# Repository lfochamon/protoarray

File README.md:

# ProtoArray: A prototype microphone array for the BeagleBone Black

This repository contains a prototype ADS131E08 cape for the BBB to be used as a microphone array (or whatever).

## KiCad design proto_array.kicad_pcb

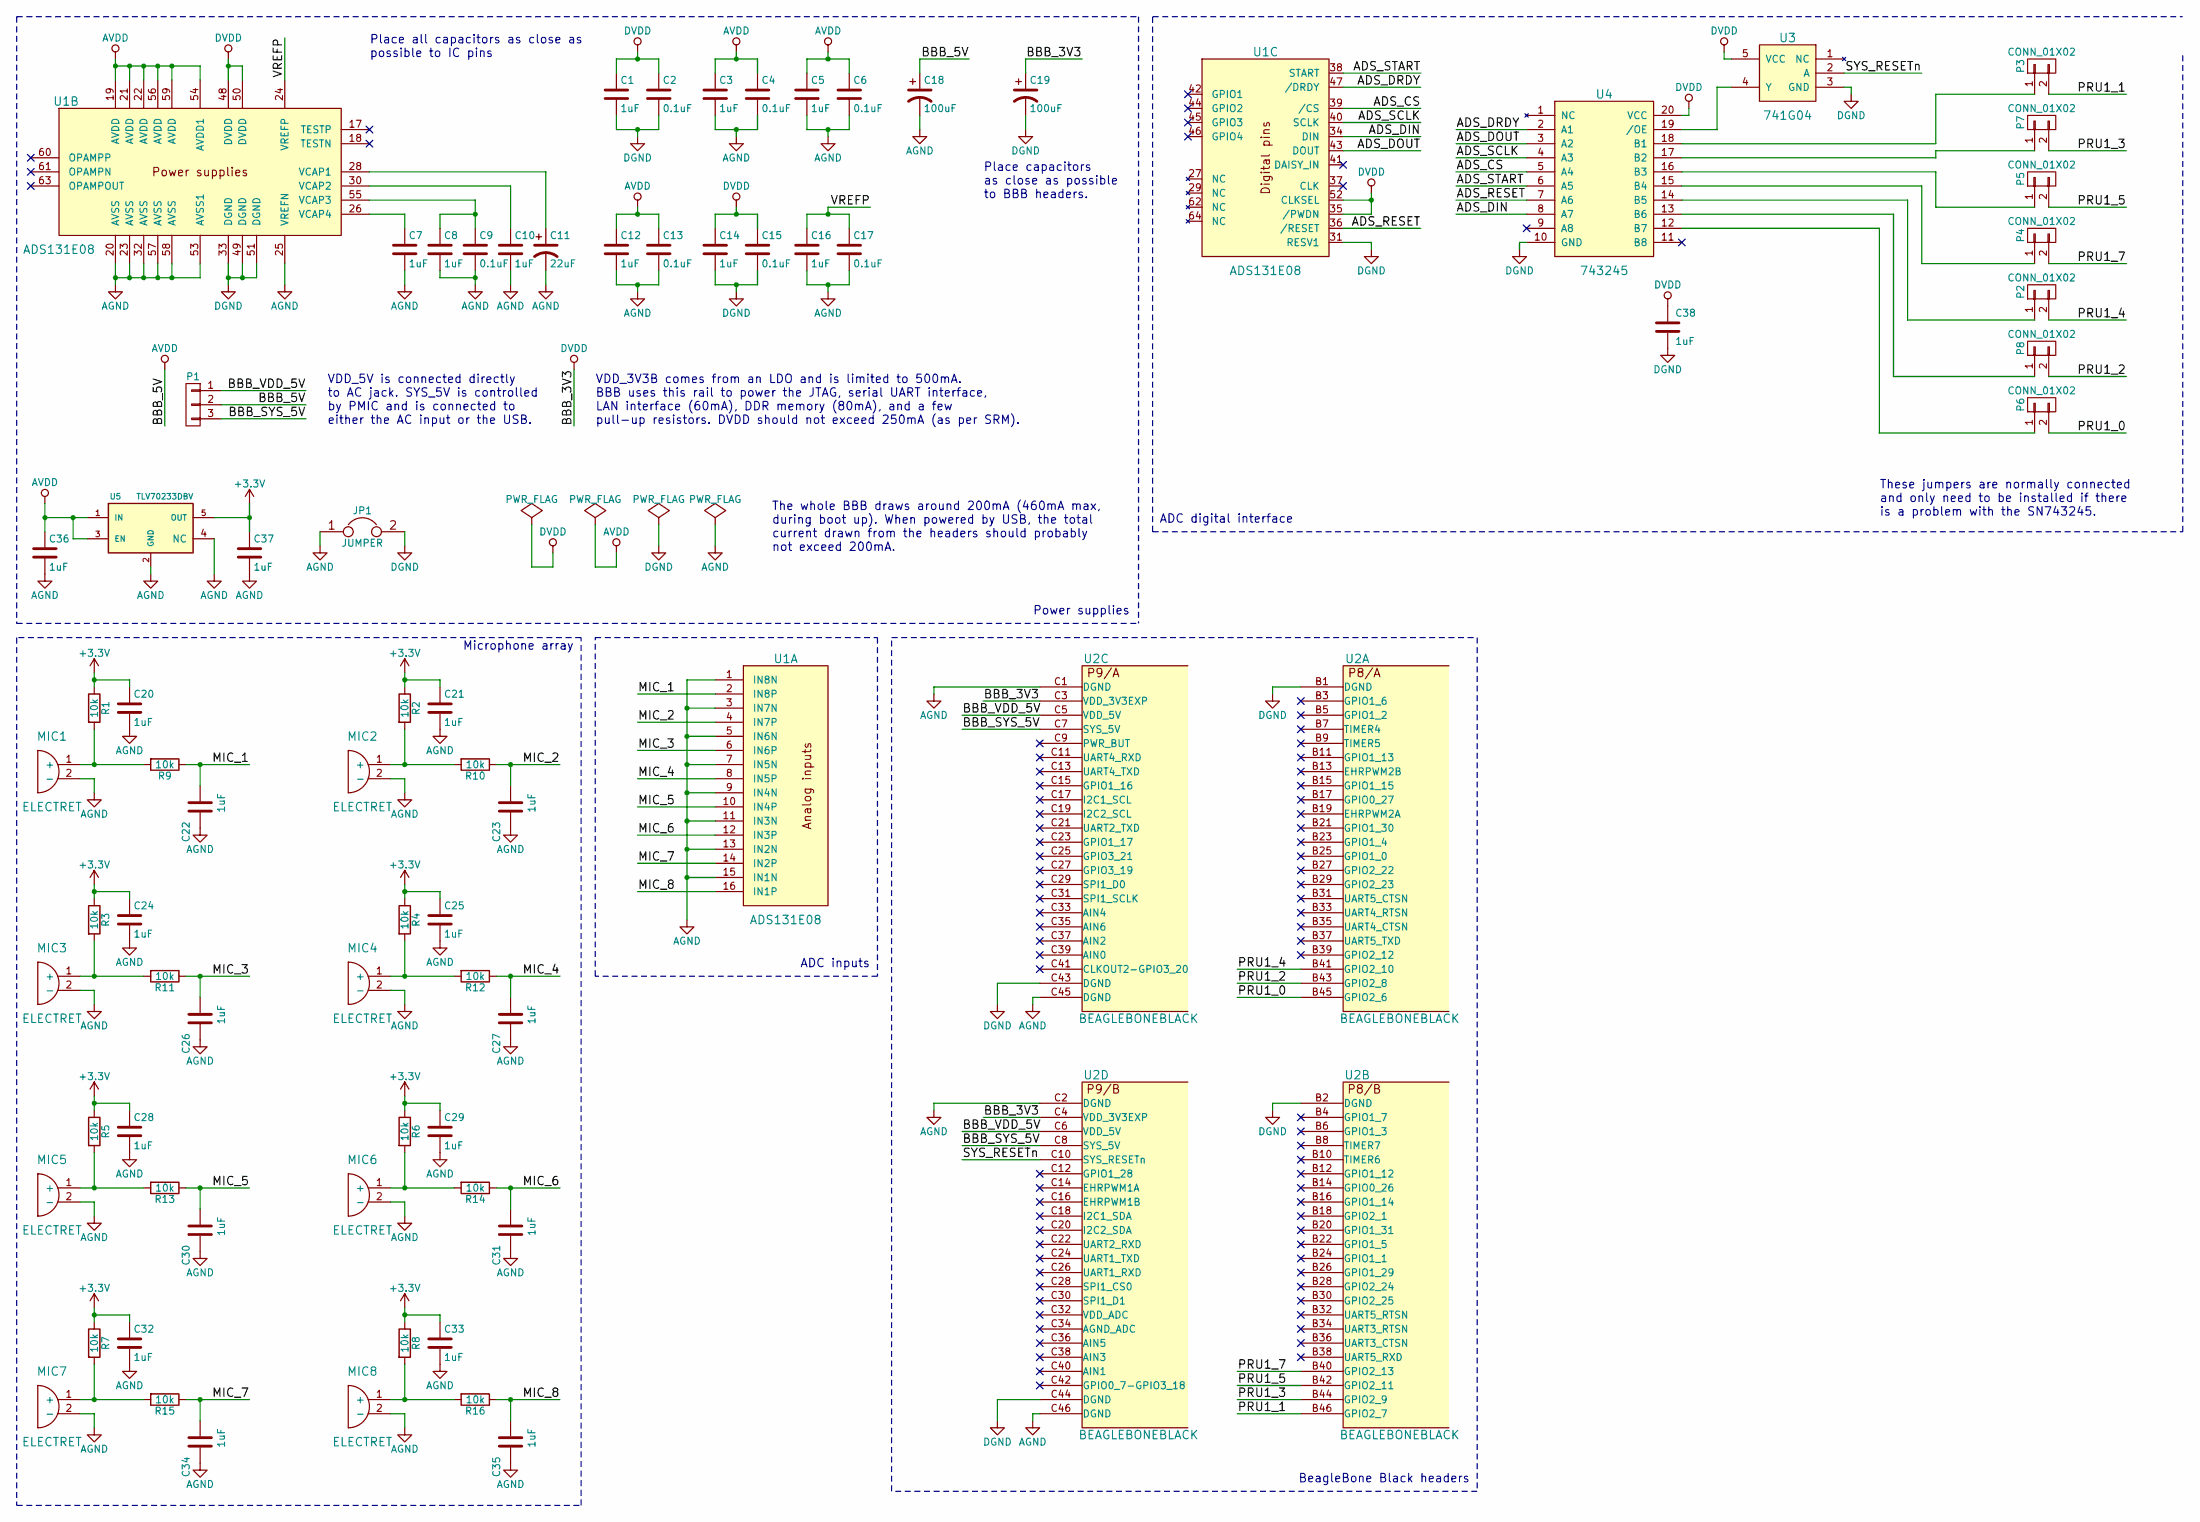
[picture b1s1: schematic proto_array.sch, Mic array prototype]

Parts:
C1, C3, C5, C7, C8, C10, C12, C14, C16, C20, C21, C22, C23, C24, C25, C26, C27, C28, C29, C30, C31, C32, C33, C34, C35, C36, C37, C38: 1uF; C_0805_HandSoldering
C2, C4, C6, C9, C13, C15, C17: 0.1uF; C_0805_HandSoldering
C11: 22uF; TantalC_SizeB_EIA-3528_HandSoldering
C18, C19: 100uF; Elko_vert_11.2x6.3mm_RM2.5_CopperClear
JP1: JUMPER; Jumper
MIC1, MIC2, MIC3, MIC4, MIC5, MIC6, MIC7, MIC8: ELECTRET; Electret_1mm
P1: CONN_01X03; Pin_Header_01x03
P2, P3, P4, P5, P6, P7, P8: CONN_01X02; Pin_Header_NC_01x02
R1, R2, R3, R4, R5, R6, R7, R8, R9, R10, R11, R12, R13, R14, R15, R16: 10k; R_0805_HandSoldering
U1: ADS131E08; LQFP-64_12x12_Pitch0.5mm_NoFid
U2: BEAGLEBONEBLACK; beagleboneblack_custom
U3: 741G04; SOTFL-5_160x50_Pitch0.5
U4: 743245; SOP-20_600x175_Pitch0.635
U5: TLV70233DBV; SOT-23-5

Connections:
+3V3: C20.1, C21.1, C24.1, C25.1, C28.1, C29.1, C32.1, C33.1, C37.1, R1.1, R2.1, R3.1, R4.1, R5.1, R6.1, R7.1, R8.1, U5.5 (OUT)
/ADS_CS: U1.39 (/CS), U4.5 (A4)
/ADS_DIN: U1.34 (DIN), U4.8 (A7)
/ADS_DOUT: U1.43 (DOUT), U4.3 (A2)
/ADS_DRDY: U1.47 (/DRDY), U4.2 (A1)
/ADS_RESET: U1.36 (/RESET), U4.7 (A6)
/ADS_SCLK: U1.40 (SCLK), U4.4 (A3)
/ADS_START: U1.38 (START), U4.6 (A5)
/BBB_SYS_5V: P1.3, U2.C7 (SYS_5V), U2.C8 (SYS_5V)
/BBB_VDD_5V: P1.1, U2.C5 (VDD_5V), U2.C6 (VDD_5V)
/MIC_1: C22.2, R9.1, U1.2 (IN8P)
/MIC_2: C23.2, R10.1, U1.4 (IN7P)
/MIC_3: C26.2, R11.1, U1.6 (IN6P)
/MIC_4: C27.2, R12.1, U1.8 (IN5P)
/MIC_5: C30.2, R13.1, U1.10 (IN4P)
/MIC_6: C31.2, R14.1, U1.12 (IN3P)
/MIC_7: C34.2, R15.1, U1.14 (IN2P)
/MIC_8: C35.2, R16.1, U1.16 (IN1P)
/PRU1_0: P6.2, U2.B45 (GPIO2_6)
/PRU1_1: P3.2, U2.B46 (GPIO2_7)
/PRU1_2: P8.2, U2.B43 (GPIO2_8)
/PRU1_3: P7.2, U2.B44 (GPIO2_9)
/PRU1_4: P2.2, U2.B41 (GPIO2_10)
/PRU1_5: P5.2, U2.B42 (GPIO2_11)
/PRU1_7: P4.2, U2.B40 (GPIO2_13)
/SYS_RESETn: U2.C10 (SYS_RESETn), U3.2 (A)
/VREFP: C16.1, C17.1, U1.24 (VREFP)
AGND: C3.2, C4.2, C5.2, C6.2, C7.2, C8.2, C9.2, C10.2, C11.2, C12.2, C13.2, C16.2, C17.2, C18.2, C20.2, C21.2, C22.1, C23.1, C24.2, C25.2, C26.1, C27.1, C28.2, C29.2, C30.1, C31.1, C32.2, C33.2, C34.1, C35.1, C36.2, C37.2, JP1.1, MIC1.2 (-), MIC2.2 (-), MIC3.2 (-), MIC4.2 (-), MIC5.2 (-), MIC6.2 (-), MIC7.2 (-), MIC8.2 (-), U1.1 (IN8N), U1.3 (IN7N), U1.5 (IN6N), U1.7 (IN5N), U1.9 (IN4N), U1.11 (IN3N), U1.13 (IN2N), U1.15 (IN1N), U1.20 (AVSS), U1.23 (AVSS), U1.25 (VREFN), U1.32 (AVSS), U1.53 (AVSS1), U1.57 (AVSS), U1.58 (AVSS), U2.C1 (DGND), U2.C2 (DGND), U2.C45 (DGND), U2.C46 (DGND), U5.2 (GND), U5.4 (NC)
AVDD: C3.1, C4.1, C5.1, C6.1, C12.1, C13.1, C18.1, C36.1, P1.2, U1.19 (AVDD), U1.21 (AVDD), U1.22 (AVDD), U1.54 (AVDD1), U1.56 (AVDD), U1.59 (AVDD), U5.1 (IN), U5.3 (EN)
DGND: C1.2, C2.2, C14.2, C15.2, C19.2, C38.2, JP1.2, U1.31 (RESV1), U1.33 (DGND), U1.49 (DGND), U1.51 (DGND), U2.B1 (DGND), U2.B2 (DGND), U2.C43 (DGND), U2.C44 (DGND), U3.3 (GND), U4.10 (GND)
DVDD: C1.1, C2.1, C14.1, C15.1, C19.1, C38.1, U1.35 (/PWDN), U1.48 (DVDD), U1.50 (DVDD), U1.52 (CLKSEL), U2.C3 (VDD_3V3EXP), U2.C4 (VDD_3V3EXP), U3.5 (VCC), U4.20 (VCC)
unnamed: C7.1, U1.26 (VCAP4)
unnamed: C8.1, C9.1, U1.55 (VCAP3)
unnamed: C10.1, U1.30 (VCAP2)
unnamed: C11.1, U1.28 (VCAP1)
unnamed: MIC1.1 (+), R1.2, R9.2
unnamed: MIC2.1 (+), R2.2, R10.2
unnamed: MIC3.1 (+), R3.2, R11.2
unnamed: MIC4.1 (+), R4.2, R12.2
unnamed: MIC5.1 (+), R5.2, R13.2
unnamed: MIC6.1 (+), R6.2, R14.2
unnamed: MIC7.1 (+), R7.2, R15.2
unnamed: MIC8.1 (+), R8.2, R16.2
unnamed: P2.1, U4.14 (B5)
unnamed: P3.1, U4.18 (B1)
unnamed: P4.1, U4.15 (B4)
unnamed: P5.1, U4.16 (B3)
unnamed: P6.1, U4.12 (B7)
unnamed: P7.1, U4.17 (B2)
unnamed: P8.1, U4.13 (B6)
unnamed: U3.4 (Y), U4.19 (/OE)

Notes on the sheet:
Place all capacitors as close as possible to IC pins
Power supplies
Microphone array
ADC inputs
BeagleBone Black headers
ADC digital interface
VDD_5V is connected directly to AC jack. SYS_5V is controlled by PMIC and is connected to either the AC input or the USB.
VDD_3V3B comes from an LDO and is limited to 500mA. BBB uses this rail to power the JTAG, serial UART interface, LAN interface (60mA), DDR memory (80mA), and a few pull-up resistors. DVDD should not exceed 250mA (as per SRM).
The whole BBB draws around 200mA (460mA max, during boot up). When powered by USB, the total current drawn from the headers should probably not exceed 200mA.
Place capacitors as close as possible to BBB headers.
These jumpers are normally connected and only need to be installed if there is a problem with the SN743245.

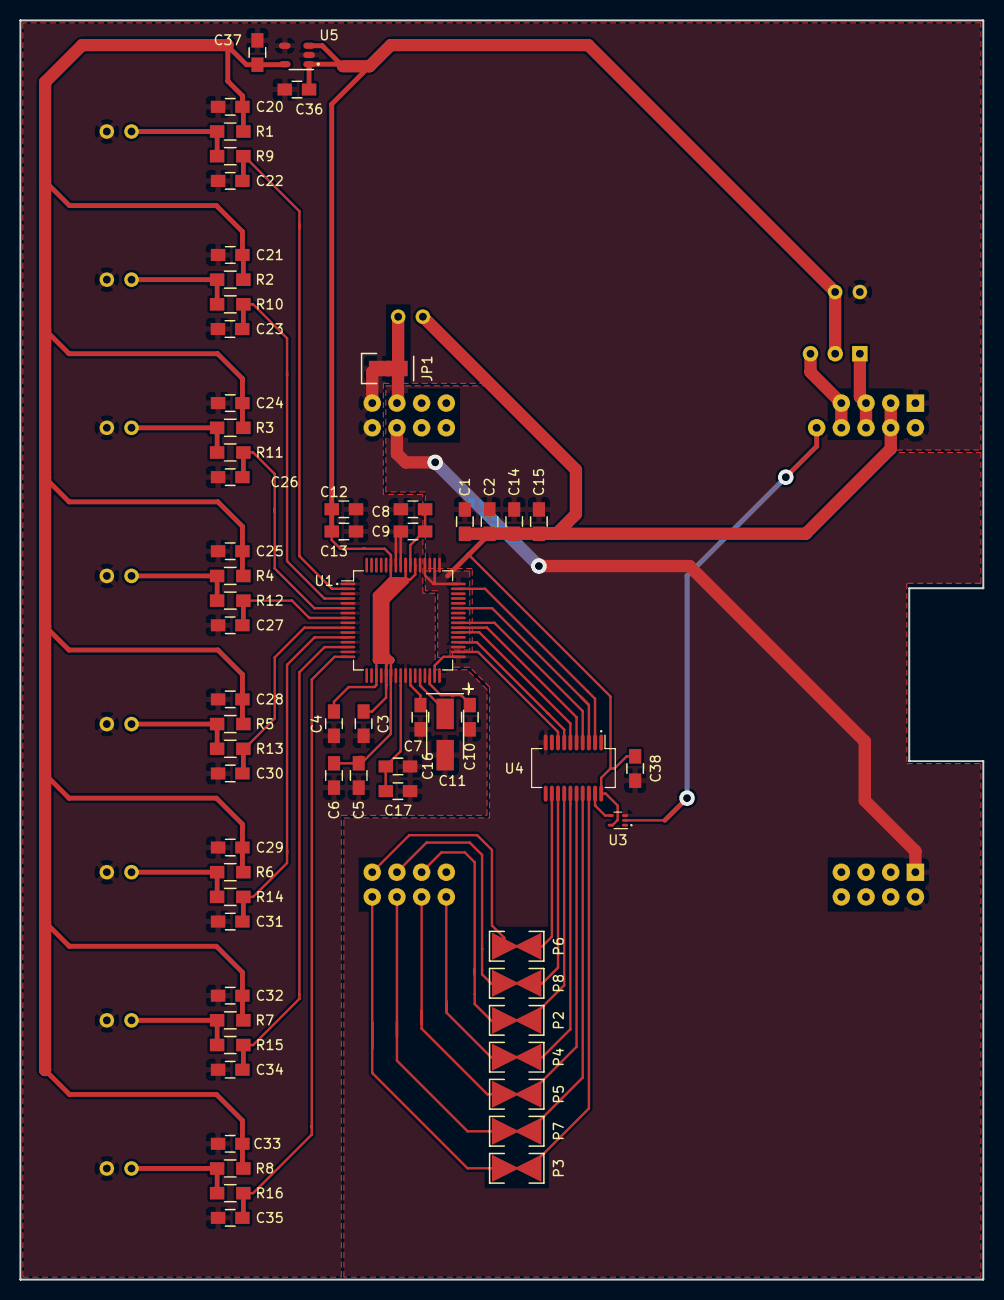
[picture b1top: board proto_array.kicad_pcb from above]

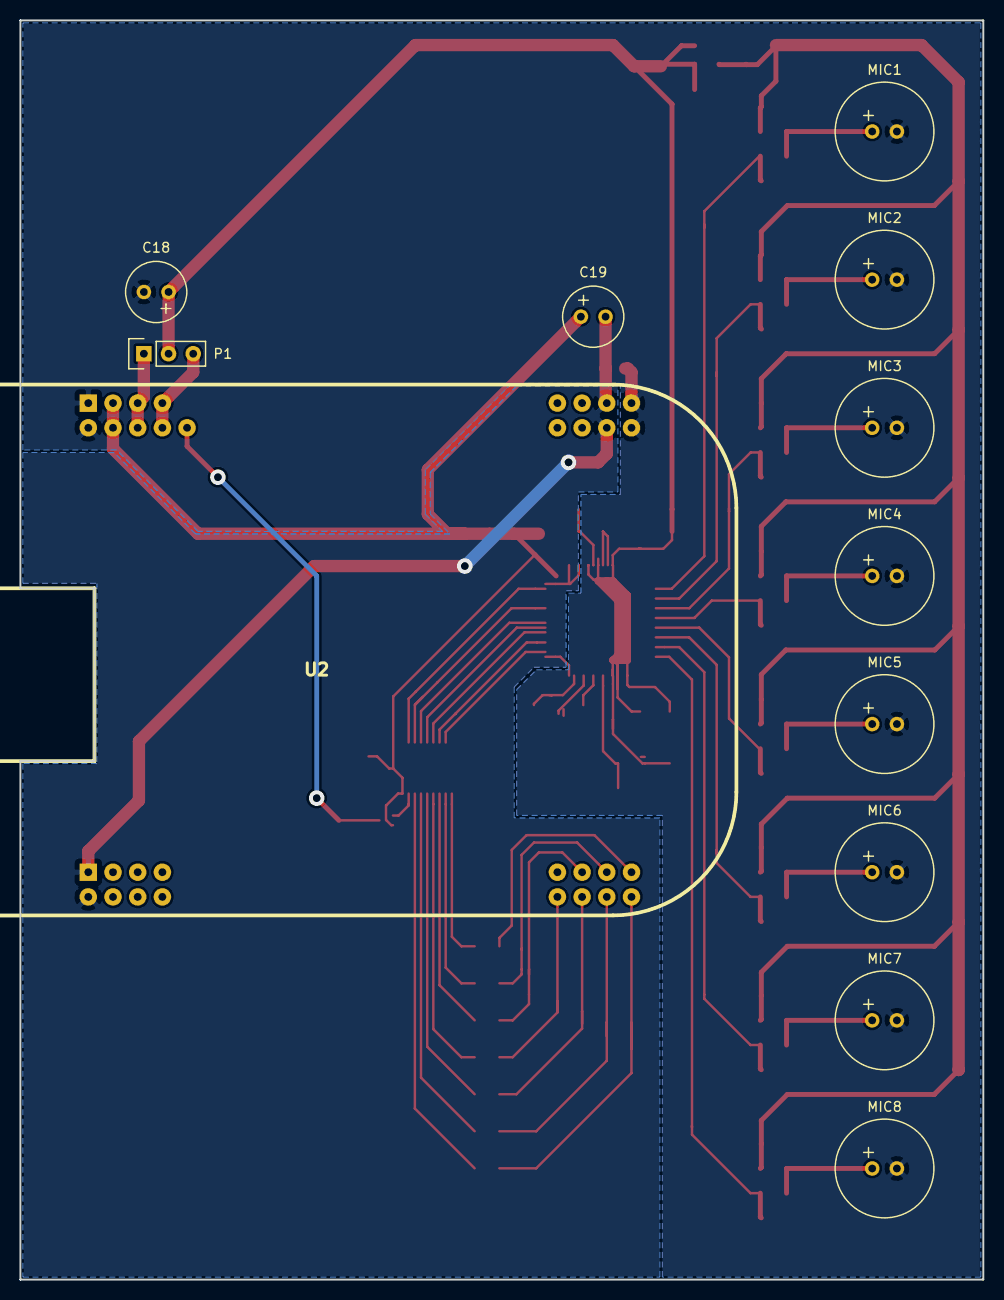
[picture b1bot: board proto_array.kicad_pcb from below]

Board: 2 copper layers, 99.1 x 129.5 mm, 76 parts (12 on the bottom side), 51 nets.

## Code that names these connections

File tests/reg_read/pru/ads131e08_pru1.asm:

; Pin definitions
SPI_SCLK            .set    5       ; PRU1_5 GPIO2_11 P8_42
SPI_MOSI            .set    0       ; PRU1_0 GPIO2_6  P8_45 (DIN)
SPI_MISO            .set    3       ; PRU1_3 GPIO2_9  P8_44 (DOUT)
SPI_CS              .set    7       ; PRU1_7 GPIO2_13 P8_40
ADS_START           .set    4       ; PRU1_4 GPIO2_10 P8_41
ADS_RESET           .set    2       ; PRU1_2 GPIO2_8  P8_43
ADS_DRDY            .set    1       ; PRU1_1 GPIO2_7  P8_46

; SPI_SCLK_DELAY = floor( (t_SCLK / 5 ns) / 4 ); SPI_SCLK_DELAY >= 3
SPI_SCLK_DELAY      .set    15

; Interrupt
PRU_INT_VALID       .set    32
PRU0_PRU1_INTERRUPT .set    1       ; PRU_EVTOUT_
PRU1_PRU0_INTERRUPT .set    2       ; PRU_EVTOUT_
PRU0_ARM_INTERRUPT  .set    3       ; PRU_EVTOUT_0
PRU1_ARM_INTERRUPT  .set    4       ; PRU_EVTOUT_1
ARM_PRU0_INTERRUPT  .set    5       ; PRU_EVTOUT_
ARM_PRU1_INTERRUPT  .set    6       ; PRU_EVTOUT_

; Name PRU register banks
XFR_BANK0           .set    10
XFR_BANK1           .set    11
XFR_BANK2           .set    12
XFR_PRU             .set    14


; Code starts here
    .text
    .retain
    .retainrefs
    .global         main

; Include ADS131 driver
    .include "ads131e08.inc"

main:
; Start up sequence for the ADS
    ADS_STARTUP

; Read in all ADS registers
    ADS_READ_ALL r1.b0, r1.b1, r1.b2, r1.b3, r2.b0, r2.b1, r2.b2, r2.b3, r3.b0, r3.b1, r3.b2, r3.b3, r4.b0, r4.b1, r4.b2, r4.b3

    XOUT    XFR_BANK0, &r1, 16                          ; Save to scratch pad
    LDI     r31.b0, PRU_INT_VALID + PRU1_PRU0_INTERRUPT ; Signal PRU0

; Stop PRU
    HALT

; Setup function calls for ADS driver
    ADS_INIT

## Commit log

2015-06-02 First commit. Schematic for mic array prototype with BBB.
2015-06-22 First commit.
2015-06-22 Simple test sending 2 buffers.
2015-06-22 Test sending full messages continuously to the PC.
2015-06-24 Rewrite using new TI's compiler assembly language.
2015-06-24 Rewrite in TI's compiler assembly language.
2015-06-25 Fix assembly to be compatible with TI's compiler.
2015-06-25 Fix assembly to be compatible with TI's compiler.
    * Fix assembly to be compatible with TI's compiler.
    + Fix error in loop filling logic.
2015-06-25 Update build files to use TI's PRU compiler.
2015-06-25 Update build files to use TI's compiler.
2015-06-25 Fix small assembly errors.
    SBCO -> SBBO and XIN/XOUT must have & in front of the register used for addressing purposes (go figure!).
2015-06-25 Removed socketInfo() function.
2015-06-25 Fix small compile warnings and errors.
2015-06-25 Add client code.
2015-06-25 Fix client code.
2015-06-25 Fix server code. Small spacing fix to PRU0.
2015-06-25 Test code is working!
2015-06-25 Fix assembly errors.
    * Fix interrupt register (r30 -> r31);
    * Use & before registers used as pointers;
    * Change dummy data;
    * Fix delay loop label.
2015-06-25 Fix compile warnings and errors.
2015-06-25 Remove socketInfo function.
2015-06-25 Fix pru functions having useless side-effects.
    * pru_start no longer prints error message: leave that to the library user.
2015-07-01 Port PRU1 code to TI's compiler.
2015-07-02 Fix IC name from ADI131 to ADS131 in code.
2015-07-02 Rename files with correct IC name (ADI -> ADS).
2015-07-02 Include Device Tree Overlay for the array.
2015-07-03 Fix comments and formatting.
2015-07-03 Fix number of bytes to import from scratchpad.
2015-07-16 Small fixes in host program.
2015-07-16 Remove delay definitions.
2015-07-16 Import ADS driver library.
    Import ADS driver library from https://github.com/lchamon/beagleads131.
2015-07-16 Add ADS register read test.
2015-07-16 Add ADS register read back test.
2015-07-17 Fix pointer cast and print formatting.
2015-07-17 Update to match new ADS driver library.
    New driver library replaces macros from the SPI library with JAL calls to save memory. Otherwise simple programs wouldn't fit inside the PRU.
2015-07-17 Add include path to build command.
2015-07-17 Update ADS driver library.
2015-07-17 Fix read back test.
    * Fix pointer cast and print format;
    * Add include path to build script;
    * Update PRU code to new ADS driver library.
2015-07-18 Remove server header.
2015-07-18 Add signal measurement tests.
2015-07-18 Footprint association.
2015-07-18 PCB design.
2015-07-18 Eliminated the headers for SPI interface to make PCB single layer.
2015-07-18 Routed AVDD. Trying to solve ground routing.
2015-07-18 * Fix PRU connections on the schematic * Reduce microphone tracks to fit ground plane * Remove fiducials from ADC IC
2015-07-18 Final PCB with one airwire.
2015-07-18 * Add ADC footprint without fiducials * Remove unused pin headers from BBB * Modify eletret footprint
2015-07-18 Final board version...
    * Fix ADC net DRC (clearance: 8 mils)
    * Fix a few track-pad clearance violations
    * Fix ground plane pours
2015-07-18 Erase SPI remaining net labels and fix unconnected pins error in schematics.
2015-07-18 Unify drill sizes (all drilling in 0.8 mm).
2015-07-18 Generate gerber files and PCB image/place.
2015-07-18 Update project file.
2015-07-18 Update tantalum capacitor (C11) package.
2015-07-21 Disable pull-up/pull-down on PRU input pins.
2015-07-21 Fix ID and CONFIG3 values in tests print outs.
2015-07-21 Bug fix in write to RAM routine.
2015-07-21 Start user registers at r1 instead of r0.
2015-07-21 Change read back test to match read test changes.
2015-07-21 Make MSG_SIZE = 1000*1024 to match PRU code.
2015-07-21 Write STAT message to RAM and increase MSG_SIZE.
2015-07-21 Use ADS_SEND_CMD and fix code formatting.
2015-07-21 Small fixes in register read test.
2015-07-21 Fix register order and print in read back test.
2015-07-21 Use more diverse settings for test.
2015-07-21 Add MSG_SIZE definition.
2015-07-21 Add MATLAB script to parse and plot signals.
2015-07-21 Update ADS driver library to import new fixes.
2015-07-21 Fix footprint for header 1x3 and add header 1x2.
2015-07-21 Remove test point and add header on PRU pins.
2015-07-21 Update PCB.
    * Remove test point
    * Add header to PRU pins
2015-07-24 Include switch for SYSBOOT pins and fix mic powering.
2015-07-24 Add SN743245 and TLV702 footprints to library.
2015-07-27 Add 741G04 and normally connected jumper footprints.
2015-07-27 Update footprints in the schematics.
2015-07-27 Remove NI resistors and include jumper between GNDs.
2015-07-27 Fix NC jumper and custom BBB footprints.
2015-07-27 Add bypass to 743245 and fix pinout of 741G04.
2015-07-27 Fix clearance on jumper and NC header footprints.
2015-07-27 Update PCB with new changes in schematics.
2015-07-28 Fix jumper footprint clearances. Still a few DRC warnings.
2015-07-28 Generate new gerbers.
2015-08-14 Fix issue with TLV schematic symbol.
2016-02-21 Move files into /Hardware folder.
2016-02-21 Add test/example programs.
2016-02-21 Move host program prototypes to /Software folder.
2016-02-21 Add pictures of prototype PCB.
2016-02-21 Add README.
